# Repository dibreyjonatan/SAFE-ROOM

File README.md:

# SAFE-ROOM
SAFE ROOM est une dispositif électronique qui permet de connaitre en temps réel, les conditions d'une pièce. A savoir la qualité d'air, la temperature, l'humidité, et la pression.  Ce projet intègre également une antenne bluetooth qui permet de transmettre sur une platform les données capteur.

# SCHEMATIQUE DU PROJET
La schématique a été réalisé avec KiCAD 9.0

# CARTE SAFE ROOM

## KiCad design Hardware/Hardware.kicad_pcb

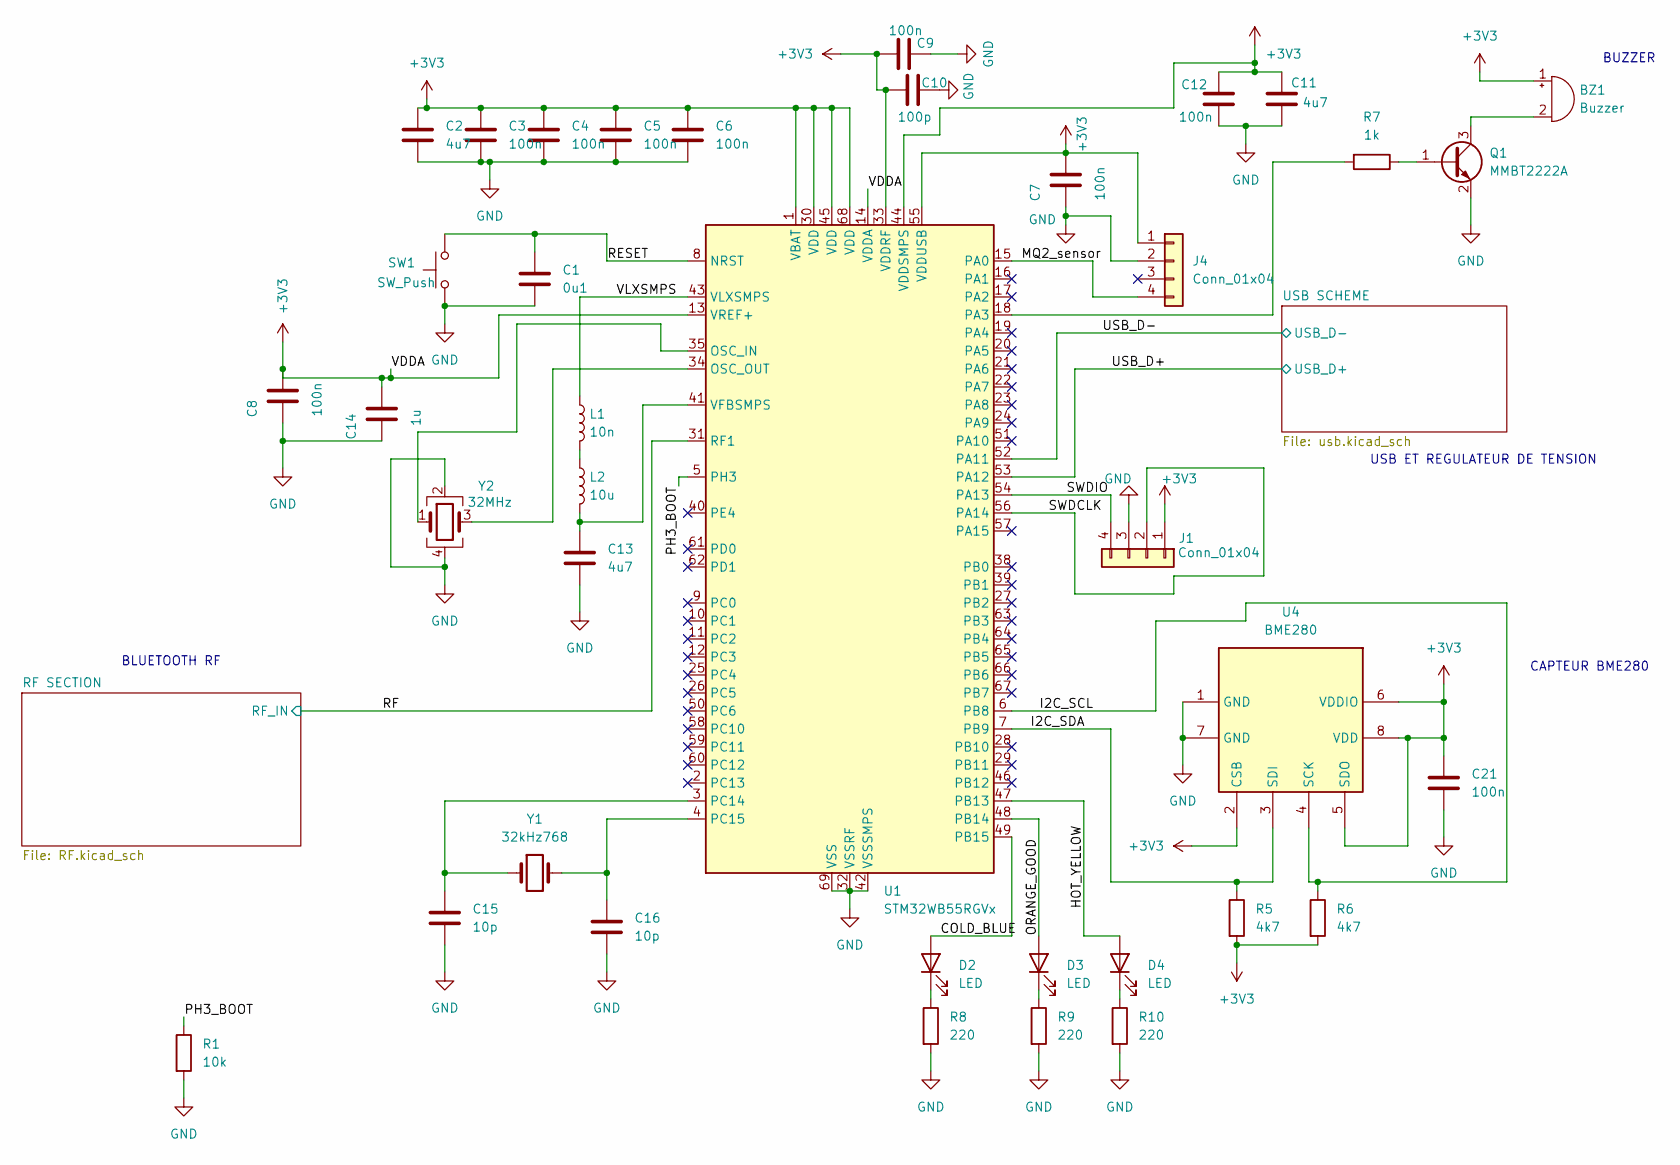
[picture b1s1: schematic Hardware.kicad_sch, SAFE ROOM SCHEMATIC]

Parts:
BZ1: Buzzer; Buzzer_12x9.5RM7.6; Manufacturer Part Number CMI-1295-85T
C1: 0u1; C_0402_1005Metric; Manufacturer Part Number 04023C104KAT2A
C2, C11, C13: 4u7; C_0603_1608Metric; Manufacturer Part Number 0603YD475MAT2A
C3, C4, C5, C6, C7, C8, C9, C12, C21: 100n; C_0402_1005Metric; Manufacturer Part Number 04023C104KAT2A
C10: 100p; C_0402_1005Metric; Manufacturer Part Number 04025A101JAT2A
C14: 1u; C_0402_1005Metric; Manufacturer Part Number GRM155R61E105KA12D
C15, C16: 10p; C_0402_1005Metric; Manufacturer Part Number 04025A100JAT4A
D2: LED; LED_D3.0mm; Manufacturer Part Number WP7113QBC/D
D3: LED; LED_D3.0mm; Manufacturer Part Number WP7113ND
D4: LED; LED_D3.0mm; Manufacturer Part Number WP7113SYD
J1, J4: Conn_01x04; PinHeader_1x04_P2.54mm_Vertical; Manufacturer Part Number TSW-112-07-TM-S
L1: 10n; L_0402_1005Metric; Manufacturer Part Number LQG15WZ10NJ02D
L2: 10u; L_0805_2012Metric; Manufacturer Part Number LQM21FN100M70L
Q1: MMBT2222A; SOT-23; Manufacturer Part Number MMBT2222A
R1: 10k; R_0402_1005Metric; Manufacturer Part Number RC0402BR-0710KL
R5, R6: 4k7; R_0402_1005Metric; Manufacturer Part Number RC0402BR-074K7L
R7: 1k; R_0402_1005Metric; Manufacturer Part Number RC0402BR-071KL
R8, R9, R10: 220; R_0402_1005Metric; Manufacturer Part Number RC0402FR-07221RL
SW1: SW_Push; SW_SPST_CK_RS282G05A3; Manufacturer Part Number RS-282G05A3-SM RT
U1: STM32WB55RGVx; QFN40P800X800X100-69N; Manufacturer Part Number STM32WB55RGV6
U4: BME280; Bosch_LGA-8_2.5x2.5mm_P0.65mm_ClockwisePinNumbering; Manufacturer Part Number BME280
Y1: 32kHz768; Crystal_SMD_2012-2Pin_2.0x1.2mm; Manufacturer Part Number NX2012SA-32.768K-STD-MUB-1
Y2: 32MHz; Crystal_SMD_2016-4Pin_2.0x1.6mm; Manufacturer Part Number NX2016SA-32M-EXS00A-CS06465

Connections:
+3V3: BZ1.1 (+), C2.1, C3.1, C4.1, C5.1, C6.1, C7.2, C8.2, C9.2, C10.2, C11.1, C12.1, C14.2, C21.1, J1.1, J4.1, R5.2, R6.2, U1.1 (VBAT), U1.13 (VREF+), U1.14 (VDDA), U1.30 (VDD), U1.33 (VDDRF), U1.44 (VDDSMPS), U1.45 (VDD), U1.55 (VDDUSB), U1.68 (VDD), U4.2 (CSB), U4.5 (SDO), U4.6 (VDDIO), U4.8 (VDD); also elsewhere on the board
/COLD_BLUE: D2.2 (A), U1.49 (PB15)
/HOT_YELLOW: D4.2 (A), U1.47 (PB13)
/I2C_SCL: R6.1, U1.6 (PB8), U4.4 (SCK)
/I2C_SDA: R5.1, U1.7 (PB9), U4.3 (SDI)
/MQ2_sensor: J4.4, U1.15 (PA0)
/ORANGE_GOOD: D3.2 (A), U1.48 (PB14)
/PH3_BOOT: R1.1, U1.5 (PH3)
/RESET: C1.1, SW1.2, U1.8 (NRST)
/RF: U1.31 (RF1); also elsewhere on the board
/SWDCLK: J1.2, U1.56 (PA14)
/SWDIO: J1.4, U1.54 (PA13)
/USB_D+: U1.53 (PA12); also elsewhere on the board
/USB_D-: U1.52 (PA11); also elsewhere on the board
/VLXSMPS: L1.1, U1.43 (VLXSMPS)
GND: C1.2, C2.2, C3.2, C4.2, C5.2, C6.2, C7.1, C8.1, C9.1, C10.1, C11.2, C12.2, C13.2, C14.1, C15.2, C16.2, C21.2, J1.3, J4.2, Q1.2 (E), R1.2, R8.2, R9.2, R10.2, SW1.1, U1.32 (VSSRF), U1.42 (VSSSMPS), U1.69 (VSS), U4.1 (GND), U4.7 (GND), Y2.2, Y2.4; also elsewhere on the board
unnamed: BZ1.2 (-), Q1.3 (C)
unnamed: D2.1 (K), R8.1
unnamed: D3.1 (K), R9.1
unnamed: D4.1 (K), R10.1
unnamed: L1.2, L2.1
unnamed: Q1.1 (B), R7.1
unnamed: U1.35 (OSC_IN), Y2.1
unnamed: U1.34 (OSC_OUT), Y2.3
unnamed: R7.2, U1.18 (PA3)
unnamed: C15.1, U1.3 (PC14), Y1.1
unnamed: C16.1, U1.4 (PC15), Y1.2
unnamed: C13.1, L2.2, U1.41 (VFBSMPS)

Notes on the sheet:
CAPTEUR BME280
USB ET REGULATEUR DE TENSION
BUZZER
BLUETOOTH RF

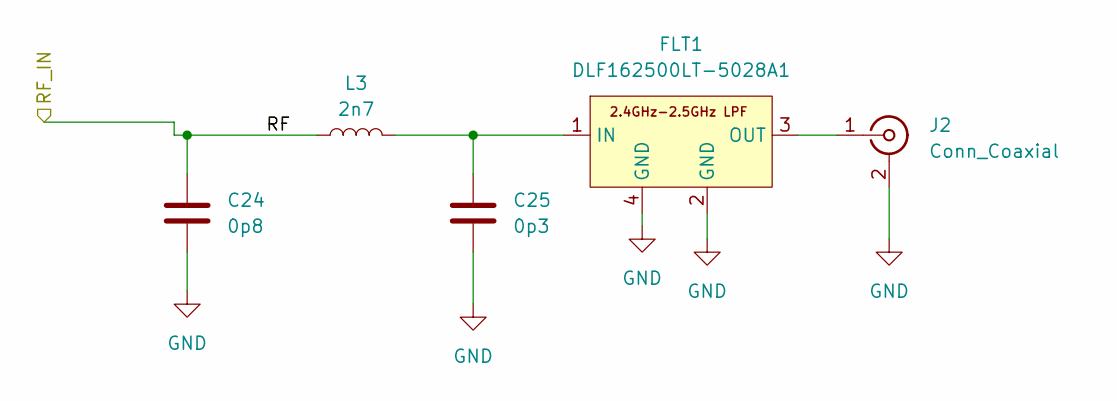
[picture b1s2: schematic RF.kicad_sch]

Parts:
C24: 0p8; C_0402_1005Metric; Manufacturer Part Number VJ0402D0R8VXBAJHT
C25: 0p3; C_0402_1005Metric; Manufacturer Part Number GRM1555C1HR30WA01D
FLT1: DLF162500LT-5028A1; FIL_DEA160915LT-1169; Manufacturer Part Number DLF162500LT-5028A1
J2: Conn_Coaxial; U.FL_Hirose_U.FL-R-SMT-1_Vertical; Manufacturer Part Number U.FL-R-SMT(01)
L3: 2n7; L_0402_1005Metric; Manufacturer Part Number LQG15HS2N7S02D

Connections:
/RF: C24.1, L3.1; also elsewhere on the board
GND: C24.2, C25.2, FLT1.2 (GND), FLT1.4 (GND), J2.2 (Ext); also elsewhere on the board
unnamed: C25.1, FLT1.1 (IN), L3.2
unnamed: FLT1.3 (OUT), J2.1 (In)

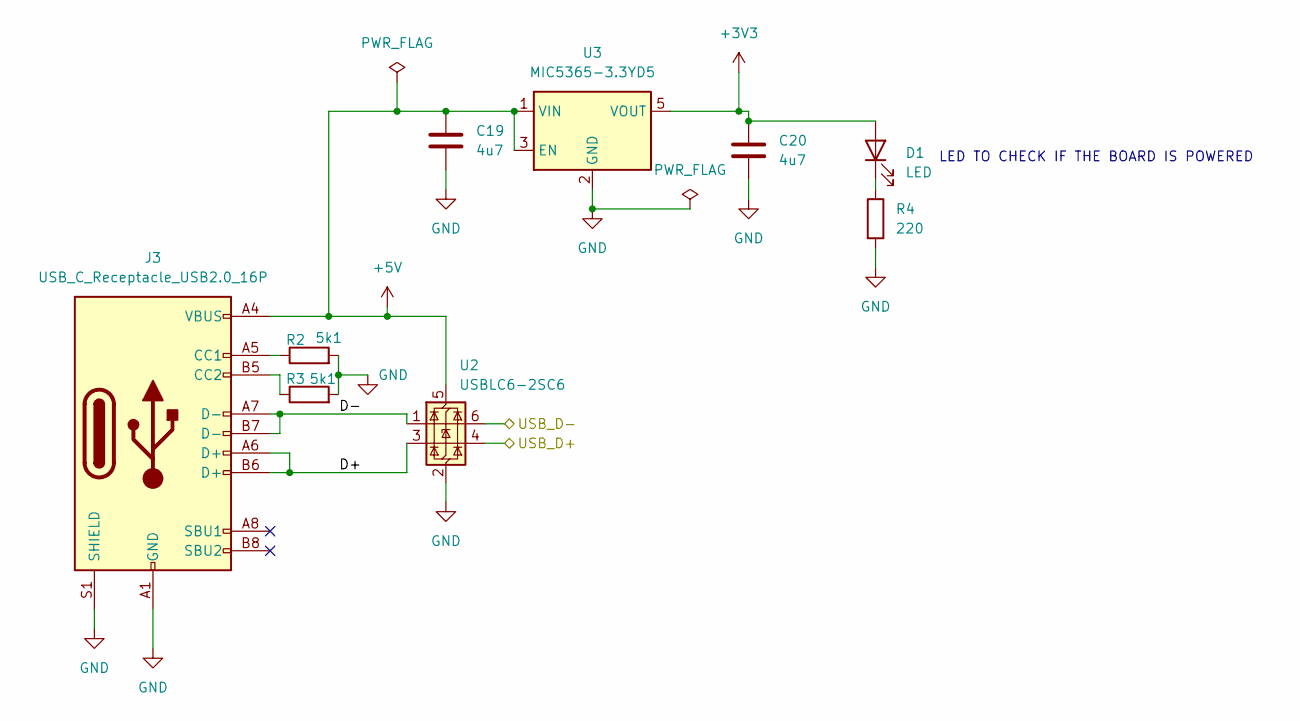
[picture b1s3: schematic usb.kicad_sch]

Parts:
C19, C20: 4u7; C_0603_1608Metric; Manufacturer Part Number 0603YD475MAT2A
D1: LED; LED_0402_1005Metric; Manufacturer Part Number 150040RS73240
J3: USB_C_Receptacle_USB2.0_16P; USB_C_Receptacle_GCT_USB4105-xx-A_16P_TopMnt_Horizontal; Manufacturer Part Number USB4105-GF-A
R2, R3: 5k1; R_0402_1005Metric; Manufacturer Part Number RC0402BR-075K1L
R4: 220; R_0402_1005Metric; Manufacturer Part Number RC0402FR-07221RL
U2: USBLC6-2SC6; SOT-23-6; Manufacturer Part Number USBLC6-2SC6
U3: MIC5365-3.3YD5; TSOT-23-5; Manufacturer Part Number MIC5365-3.3YD5-TR

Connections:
+3V3: C20.1, D1.2 (A), U3.5 (VOUT); also elsewhere on the board
+5V: C19.1, J3.A4 (VBUS), J3.A9 (VBUS), J3.B4 (VBUS), J3.B9 (VBUS), U2.5 (VBUS), U3.1 (VIN), U3.3 (EN)
/USB SCHEME/D+: J3.A6 (D+), J3.B6 (D+), U2.3 (I/O2)
/USB SCHEME/D-: J3.A7 (D-), J3.B7 (D-), U2.1 (I/O1)
/USB_D+: U2.4 (I/O2); also elsewhere on the board
/USB_D-: U2.6 (I/O1); also elsewhere on the board
GND: C19.2, C20.2, J3.A1 (GND), J3.A12 (GND), J3.B1 (GND), J3.B12 (GND), J3.S1 (SHIELD), R2.2, R3.2, R4.2, U2.2 (GND), U3.2 (GND); also elsewhere on the board
unnamed: D1.1 (K), R4.1
unnamed: J3.A5 (CC1), R2.1
unnamed: J3.B5 (CC2), R3.1

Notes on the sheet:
LED TO CHECK IF THE BOARD IS POWERED

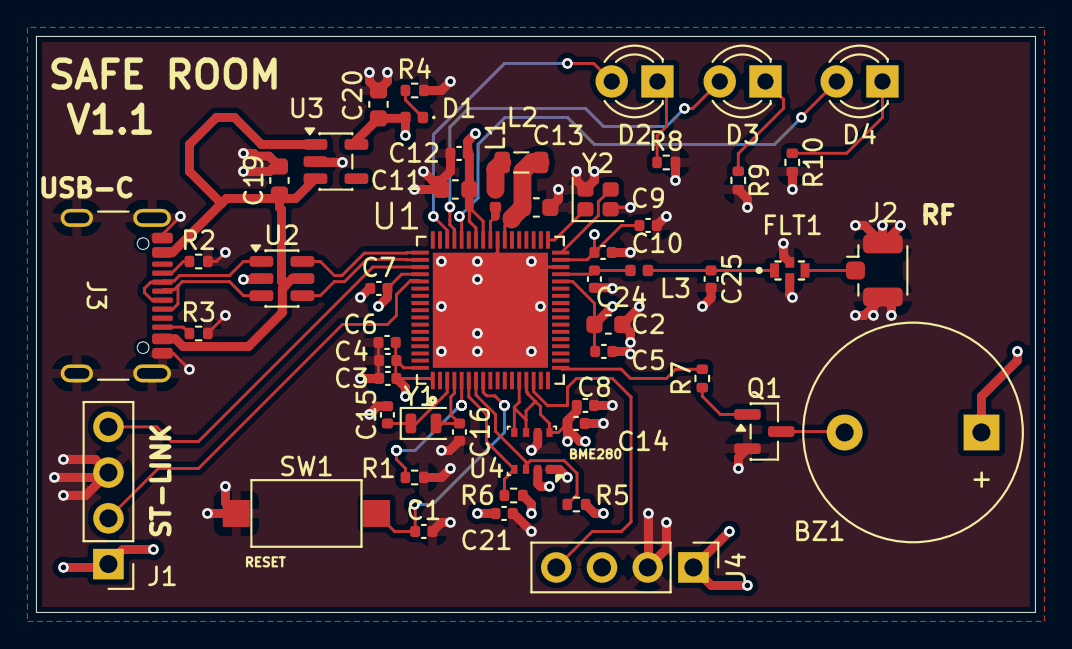
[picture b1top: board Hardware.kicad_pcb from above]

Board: 4 copper layers, 55.5 x 32.0 mm, 52 parts (0 on the bottom side), 36 nets.

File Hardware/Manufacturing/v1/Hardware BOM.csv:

"Reference","Qty","Value","Footprint","Datasheet","Manufacturer","Manufacturer Part Number"
"BZ1","1","Buzzer","Buzzer_Beeper:Buzzer_12x9.5RM7.6","https://www.mouser.fr/datasheet/3/6118/1/cmi_1295_85t.pdf","Same Sky","CMI-1295-85T"
"C1","1","0u1","Capacitor_SMD:C_0402_1005Metric","https://datasheets.kyocera-avx.com/KGM_X7R.pdf","KYOCERA AVX","04023C104KAT2A"
"C2,C11,C13,C19,C20","5","4u7","Capacitor_SMD:C_0603_1608Metric","https://datasheets.kyocera-avx.com/cx5r.pdf","KYOCERA AVX","0603YD475MAT2A"
"C3,C4,C5,C6,C7,C8,C9,C12,C21","9","100n","Capacitor_SMD:C_0402_1005Metric","https://datasheets.kyocera-avx.com/KGM_X7R.pdf","KYOCERA AVX","04023C104KAT2A"
"C10","1","100p","Capacitor_SMD:C_0402_1005Metric","https://datasheets.kyocera-avx.com/C0GNP0-KGM.pdf","KYOCERA AVX","04025A101JAT2A"
"C14","1","1u","Capacitor_SMD:C_0402_1005Metric","https://www.mouser.fr/datasheet/3/76/1/GRM155R61E105KA12-01A.pdf","Murata Electronics","GRM155R61E105KA12D"
"C15,C16","2","10p","Capacitor_SMD:C_0402_1005Metric","https://datasheets.kyocera-avx.com/C0GNP0-KGM.pdf","KYOCERA AVX","04025A100JAT4A"
"C24","1","0p8","Capacitor_SMD:C_0402_1005Metric","https://www.vishay.com/docs/45239/vjhifreqht.pdf","Vishay / Vitramon","VJ0402D0R8VXBAJHT"
"C25","1","0p3","Capacitor_SMD:C_0402_1005Metric","https://pim.murata.com/asset/pim4/ceramicCapacitorSMD/GRM155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","Murata Electronics","GRM1555C1HR30WA01D"
"D1","1","LED","LED_SMD:LED_0402_1005Metric","https://www.we-online.com/components/products/datasheet/1500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","Wurth Elektronik","150040RS73240"
"D2,D3,D4","3","LED","LED_THT:LED_D3.0mm","https://www.mouser.fr/ProductDetail/Kingbright/WP7113ND?qs=C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,https://www.mouser.fr/ProductDetail/Kingbright/WP7113QBC-D?q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,https://www.snapeda.com/parts/WP7113SYD/Kingbright/datasheet/","Kingbright,Kingbright ","WP7113ND,WP7113QBC/D,WP7113SYD"
"FLT1","1","DLF162500LT-5028A1","my_personnal_Library_footprint:FIL_DEA160915LT-1169","https://product.tdk.com/system/files/dam/doc/product/rf/rf/f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","TDK","DLF162500LT-5028A1"
"J1,J4","2","Conn_01x04","Connector_PinHeader_2.54mm:PinHeader_1x04_P2.54mm_Vertical","https://www.snapeda.com/parts/TSW-112-07-TM-S/Samtec/datasheet/","SAMTEC","TSW-112-07-TM-S "
"J2","1","Conn_Coaxial","Connector_Coaxial:U.FL_Hirose_U.FL-R-SMT-1_Vertical","https://www.mouser.com/catalog/specsheets/hiros04491-1.pdf","Hirose Connector","U.FL-R-SMT(01)"
"J3","1","USB_C_Receptacle_USB2.0_16P","Connector_USB:USB_C_Receptacle_GCT_USB4105-xx-A_16P_TopMnt_Horizontal","https://www.usb.org/sites/default/files/documents/usb_type-c.zip","GCT","USB4105-GF-A"
"L1","1","10n","Inductor_SMD:L_0402_1005Metric","https://www.mouser.fr/datasheet/3/76/2/JELF243B_9117.pdf","Murata Electronics","LQG15WZ10NJ02D"
"L2","1","10u","Inductor_SMD:L_0805_2012Metric","https://www.mouser.fr/datasheet/3/76/2/JELF243B_0011.pdf","Murata Electronics","LQM21FN100M70L"
"L3","1","2n7","Inductor_SMD:L_0402_1005Metric","https://www.mouser.fr/datasheet/3/76/2/JELF243B_0010.pdf","Murata Electronics","LQG15HS2N7S02D"
"Q1","1","MMBT2222A","Package_TO_SOT_SMD:SOT-23","https://assets.nexperia.com/documents/data-sheet/MMBT2222A.pdf","Diotec Semiconductor","MMBT2222A"
"R1","1","10k","Resistor_SMD:R_0402_1005Metric","https://www.mouser.fr/datasheet/3/508/1/PYu-RC_Group_51_RoHS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","YAGEO","RC0402BR-0710KL"
"R2,R3","2","5k1","Resistor_SMD:R_0402_1005Metric","https://www.mouser.fr/ProductDetail/YAGEO/RC0402BR-075K1L?qs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","YAGEO","RC0402BR-075K1L"
"R4,R8,R9,R10","4","220","Resistor_SMD:R_0402_1005Metric","https://www.mouser.com/catalog/specsheets/YAGEO_PYu_RC_Group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","YAGEO","RC0402FR-07221RL"
"R5,R6","2","4k7","Resistor_SMD:R_0402_1005Metric","https://snapeda.s3.amazonaws.com/datasheet/Yageo_RC_Series_R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","YAGEO","RC0402BR-074K7L"
"R7","1","1k","Resistor_SMD:R_0402_1005Metric","https://www.snapeda.com/parts/RC0402BR-071KL/Yageo/view-part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","YAGEO","RC0402BR-071KL"
"SW1","1","SW_Push","Button_Switch_SMD:SW_SPST_CK_RS282G05A3","https://www.mouser.com/catalog/specsheets/RS-282G05A-SM_RT.pdf","C&K","RS-282G05A3-SM RT"
"U1","1","STM32WB55RGVx","my_personnal_Library_footprint:QFN40P800X800X100-69N","https://www.st.com/resource/en/datasheet/stm32wb55cc.pdf","STMicroelectronics","STM32WB55RGV6"
"U2","1","USBLC6-2SC6","Package_TO_SOT_SMD:SOT-23-6","https://www.st.com/resource/en/datasheet/usblc6-2.pdf","STMicroelectronics","USBLC6-2SC6"
"U3","1","MIC5365-3.3YD5","Package_TO_SOT_SMD:TSOT-23-5","https://ww1.microchip.com/downloads/aemDocuments/documents/A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","Microchip Technology","MIC5365-3.3YD5-TR"
"U4","1","BME280","Package_LGA:Bosch_LGA-8_2.5x2.5mm_P0.65mm_ClockwisePinNumbering","https://www.bosch-sensortec.com/media/boschsensortec/downloa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","Bosch Sensortec","BME280"
"Y1","1","32kHz768","Crystal:Crystal_SMD_2012-2Pin_2.0x1.2mm","https://www.mouser.fr/datasheet/3/1591/1/NDKX01_00006_en.pdf","NDK","NX2012SA-32.768K-STD-MUB-1"
"Y2","1","32MHz","Crystal:Crystal_SMD_2016-4Pin_2.0x1.6mm","https://www.ndk.com/en/products/upload/lineup/pdf/NDKX03-000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","NDK","NX2016SA-32M-EXS00A-CS06465"

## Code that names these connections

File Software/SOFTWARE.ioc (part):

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Mcu.Name=STM32WB55RGVx
Mcu.Package=VFQFPN68
Mcu.UserName=STM32WB55RGVx
PA11.Mode=Device
PA11.Signal=USB_DM
PA12.Mode=Device
PA12.Signal=USB_DP
PA3.Signal=S_TIM2_CH4
PB13.Signal=GPIO_Output
PB14.Signal=GPIO_Output
PB15.Signal=GPIO_Output
PB8.Mode=I2C
PB8.Signal=I2C1_SCL
PB9.Mode=I2C
PB9.Signal=I2C1_SDA
PC14-OSC32_IN.Mode=LSE-External-Oscillator
PC14-OSC32_IN.Signal=RCC_OSC32_IN
PC15-OSC32_OUT.Mode=LSE-External-Oscillator
PC15-OSC32_OUT.Signal=RCC_OSC32_OUT
RCC.HSE_VALUE=32000000
RCC.SYSCLKFreq_VALUE=32000000
RCC.SYSCLKSource=RCC_SYSCLKSOURCE_HSE
board=custom

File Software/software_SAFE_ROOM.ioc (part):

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Mcu.Name=STM32WB55RGVx
Mcu.Package=VFQFPN68
Mcu.UserName=STM32WB55RGVx
PA11.Mode=Device
PA11.Signal=USB_DM
PA12.Mode=Device
PA12.Signal=USB_DP
PA13.Mode=Serial_Wire
PA13.Signal=SYS_JTMS-SWDIO
PA14.Mode=Serial_Wire
PA14.Signal=SYS_JTCK-SWCLK
PB13.Signal=GPIO_Output
PB14.Signal=GPIO_Output
PB15.Signal=GPIO_Output
PC14-OSC32_IN.Mode=LSE-External-Oscillator
PC14-OSC32_IN.Signal=RCC_OSC32_IN
PC15-OSC32_OUT.Mode=LSE-External-Oscillator
PC15-OSC32_OUT.Signal=RCC_OSC32_OUT
RCC.HSE_VALUE=32000000
RCC.SYSCLKFreq_VALUE=32000000
board=custom

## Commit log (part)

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2026-05-05 [Démarrage]: Création des fichiers de schématique dans KiCAD
2026-05-06 [Nettoyage] : J'enlève des fichiers autogénéré par KiCaD
2026-05-06 [Ajout] : Ajout du microcontrolleur STM32WB55RG utilisé dans le projet
2026-05-06 [ST-LINK CONNEXION] : Ajout de la connexion ST-LINK pour téléverser le programme finale, il faut une connexion ST-LINK. La pin PA13 c'est pour la data ( SWDIO) La pin PA14 c'est pour l'horloge (SWCLK)
2026-05-06 [RESET]: Ajout du bouton reset et de la capacité pour filtrer les oscillations du bouton
2026-05-07 [DOCUMENTATION] : Documentation officielle de ST Microelectronics qui sert de guide pour la réalisation du système
2026-05-07 [PARTIE ALIMENTATION] : Mise en place des condensateur de découplage pour les alimentations VDD, VBAT, VDDA, VREF, VDDRF et VDSMPS. Les consignes des valeurs des condensateur de découplage sont donné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
2026-05-07 [Ajout des montages d'Oscillateurs et du Montage RF] Pour concevoir les montages d'oscillateur on utilise le document applicative de ST. Pour concevoir le montage RF, on a également utilisé le meme d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
2026-05-07 [Création de symbole, importation d'empreinte et Model 3D du filtre DLF162500LT-5028A1 depuis SnapMagic ] le filtre DLF162500LT-5028A1 n'a pas de modèle de symbole, donc je l'ai construite et puis j'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
2026-05-07 [BOOT] : Pour que la carte fonctionne bien, on met une résistance pull down à PH3_BOOT, ce qui permet au microcontroleur de continuer son execution normalement
2026-05-07 [Montage USB] : Montage de l'USB type C avec une protection ESD La protection ESD utilisé ici est l'USBLC6-2SC6 et le document pdf utilisé ici donne des indications sur comment le branché et sur son 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
2026-05-07 [Hierachisation] hierachisation de la schématique et ajout de l'USB
2026-05-07 [Alimentation de la Carte]: Source provient de l'USB L'USB fournit une tension d'alimentation de 5V, et pour l'exploiter j'utilise un régulateur de tension stable en 3.3V. Le régulateur utilisé est l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
2026-05-07 [Doc]: Datasheet du regulateur qui donne des explications quant au montage. On peut utiliser une capacité de min 1uF, donc moi j'ai utilisé une de 4.7uF
2026-05-08 [Doc]: Documentation du capteur BME280 La documentation de ce capteur permet de réaliser le montage convennable et d'obtenir l'adresse I2C du capteur. Cette adresse est 0x77.
2026-05-08 [Realisation] : Regulateur de Tension, Capteur BME280, Buzzer, MQ2 et Leds indicateurs.
    Dans cette phase, j'ai réalisé les montages suivantes ;
    Regulateur de Tension : La tension d'alimentation du système vient de
    l'USB, donc en utilisant un regulateur de tension, on parvient à
    abaisser la tension à 3.3V
    Capteur BME280 : Le montage est réalisé comme recommandé par le
    fabricant Bosch. En y précisant les résistance pull up pour le protocol
2026-05-11 [RECOVERY FILE ] : La schématique RF n'était pas sauvegarder, donc elle a été perdu sous KICAD, mais j'ai pu l'avoir avec git au commit b7ce921fafebfe8b7fab3bae224a219c4f653a9d
2026-05-11 [EXECUTION ERC] : Le check électrique a bien marché sauf une erreur persistante sur VLXSMPS ce qui est un défaut du symbole créé et non du montage de découplage proposé par ST Microelectronics
2026-05-11 [FOOTPRINT ASSIGNMENT] : Ajout des footprints à chaque élément
2026-05-11 [FOOTPRINT ASSIGNMENT] : J'ai ajouté le +5V flag de l'USB, j'ai ajouté des labels pour avoir un netclass plus consistent
2026-05-12 [VERIFICATION, CORRECTION DES FOOTPRINTS ET MODELES 3D, ET ETABLISSEMENT DES REGLES DE DESIGN DU PCB]
    Le but de cette partie est de démarrer la phase du routage PCB.
    Je concois un PCB 4 couches ici, et il y'a des montages hyperfrequences
    donc il faut prendre en compte l'impédence de la ligne dans le design.
    Il y'a également la ligne USB qui doit aussi etre une ligne 50 Ohm
    adapté avec une impédance différentielle de 90 Ohm.
    Une phase essentielle a été de calculer la largeur de la piste dans les
2026-05-13 [PLACEMENT DES COMPOSANT ET DIMENSIONNEMENT] : Avant de désigner le type de signal à chaque couche et commencer le routage, j'ai d'abord commencer par organiser les composants selon la schématique et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
2026-05-13 [CORRECTION DES ERREURS SOLDER MASK] : Correction et attribution des valeurs de solder mask avec les valeurs correct de PCB Way
2026-05-13 [ROUTAGE ET CONTROL DRC] : J'ai routé la carte sur 4 couches. F.cu layer : c'est la prémière couche In1.cu layer: c'est le plan de masse In2.cu layer : c'est le plan de tension 3.3V B.cu layer : c'es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
    J'ai routé le PCB ensuite,j'ai effectué le Test DRC, puis j'ai corrigé
    les bug manifeste.
2026-05-13 [ANNOTATION DU DESIGN]: Annotation des module present sur la carte
2026-05-14 [Bill of Materials(BOM)]: Remplissage des informations tels que : manufacturer part number, manufacturer et la documentation du composant concerné. le BOM sera envoyé avec le fichier Geber au fabrica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
2026-05-14 [PREPARATION DES FICHIERS DE COMMANDES] : Generation de fichier de placement et de fichier gebers. J'ai généré le fichier de placement des composants selon l'origine de la grille. J'ai également géné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
2026-05-14 [DOCUMENTATION] : Ajout des schémas explicatives dans le README.md
2026-05-15 [CORRECCTION DU PCB] : J'ai corrigé le PCB après avoir discuter avec le Fabricant PCB Way, j'ai corrigé le footprint de la capacité C14 avec ce qui correspond à ce qui est vendu par mouser electronic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
2026-05-19 [MOD] : Changement de l'empreinte des connecteurs 01x04 pour celui de 2.54mm, et adjustement de la schématique du RF
2026-05-19 [VERSION 1] : Prémière version du geber, après discussion avec PCBWay, j'ai du faire des changements de la schématique du connecteur 01x04
2026-05-19 [Version Finale] : Après Correction et readjustement du PCB, voici la version produite
